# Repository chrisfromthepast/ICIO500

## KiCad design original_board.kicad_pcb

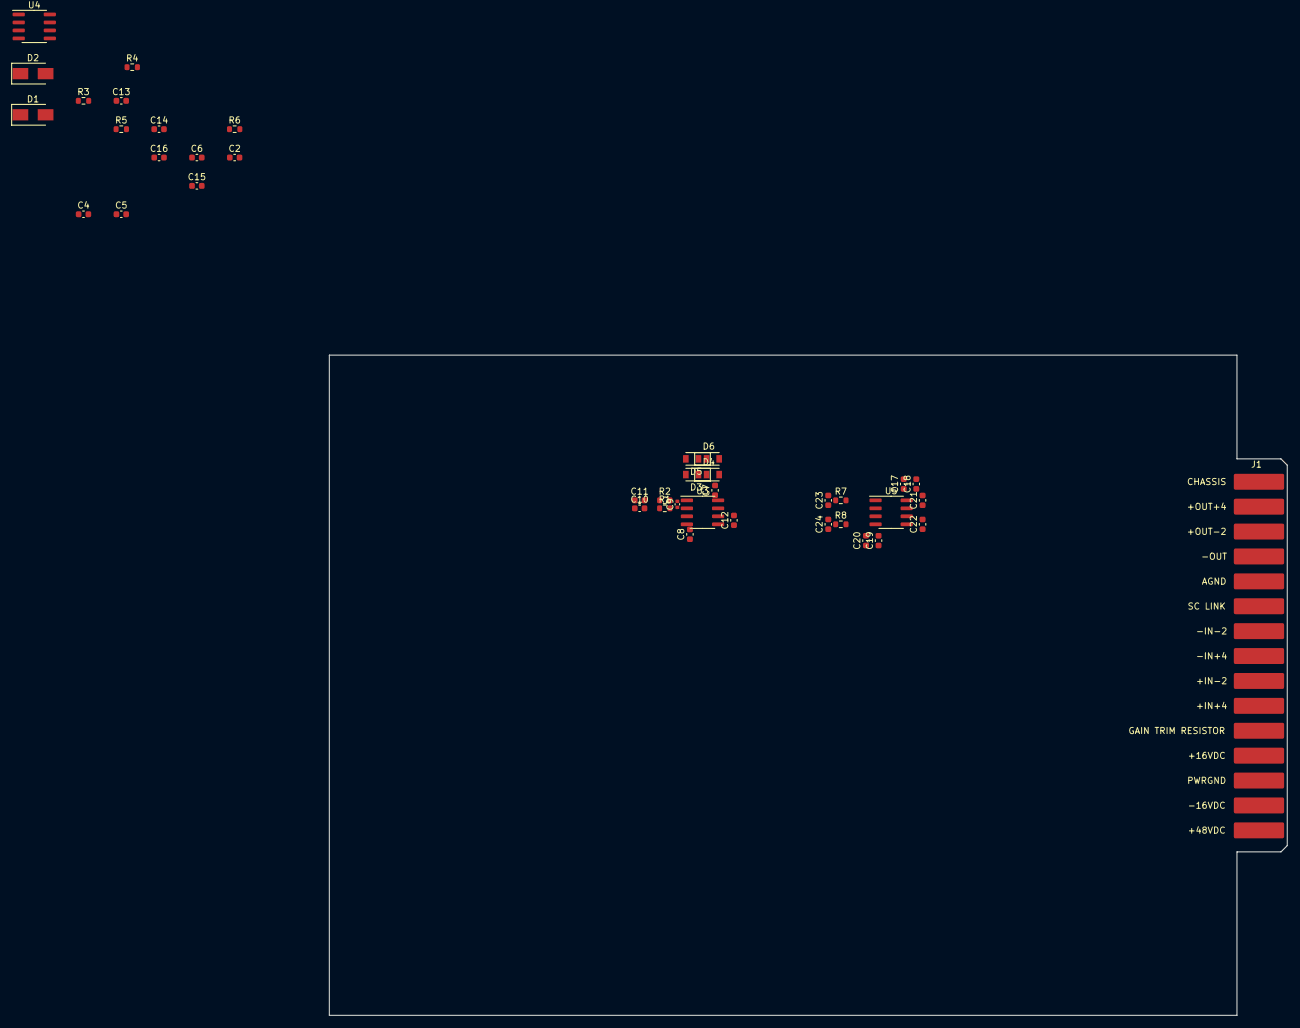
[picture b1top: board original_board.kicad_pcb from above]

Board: 2 copper layers, 152.3 x 105.0 mm, 40 parts (0 on the bottom side), 23 nets, no tracks yet.

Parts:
C2, C4, C5, C6, C7, C8, C10, C11, C12, C13, C14, C15, C16, C17, C18, C19, C20, C21, C22, C23, C24: C0603
C9: C0402
D1, D2: ?; D_SMA
D3, D4, D5, D6: ?; D_SOD-123
J1: EDA 306; EDA_306
R1, R2, R3, R4, R5, R6, R7, R8: R0603
U3, U4, U5: ?; SOIC-8_3.9x4.9mm_P1.27mm

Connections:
audio_out: R3.1, U3.7
audio_out_to_1646: C16.1, R6.1, U4.7, U5.5
cm: C12.1, U3.6
daisy_5v_power: C5.1, C6.1
daisy_audio_in: C15.1, R4.1, U4.1
daisy_digital_gnd: C5.2, C6.2
driver.r_zobel_minus-vcc: C24.1, R8.2
driver.r_zobel_plus-vcc: C23.1, R7.2
gnd: C2.2, C4.2, C7.2, C8.2, C13.2, C14.2, C17.2, C18.2, C19.2, C20.2, C23.2, C24.2, U3.1, U5.4
in_minus: C11.2, U3.2
in_minus_1: C15.2, R3.2, R4.2, U4.2
in_minus_2: C16.2, R5.2, R6.2, U4.6
in_plus: C10.2, U3.3
out_minus: C22.1, R8.1, U5.3
out_plus_4dbu: C21.1, R7.1, U5.1
receiver.r_rf_minus-vcc: C9.2, C11.1, R2.2
receiver.r_rf_plus-vcc: C9.1, C10.1, R1.2
sense_minus: C22.2, U5.7
sense_plus: C21.2, U5.8
sm: C12.2, U3.5
v_bias_2v5: U4.3, U4.5
v_minus: C4.1, C8.1, C14.1, C19.1, C20.1, U3.4, U4.4, U5.2
v_plus: C2.1, C7.1, C13.1, C17.1, C18.1, U3.8, U4.8, U5.6

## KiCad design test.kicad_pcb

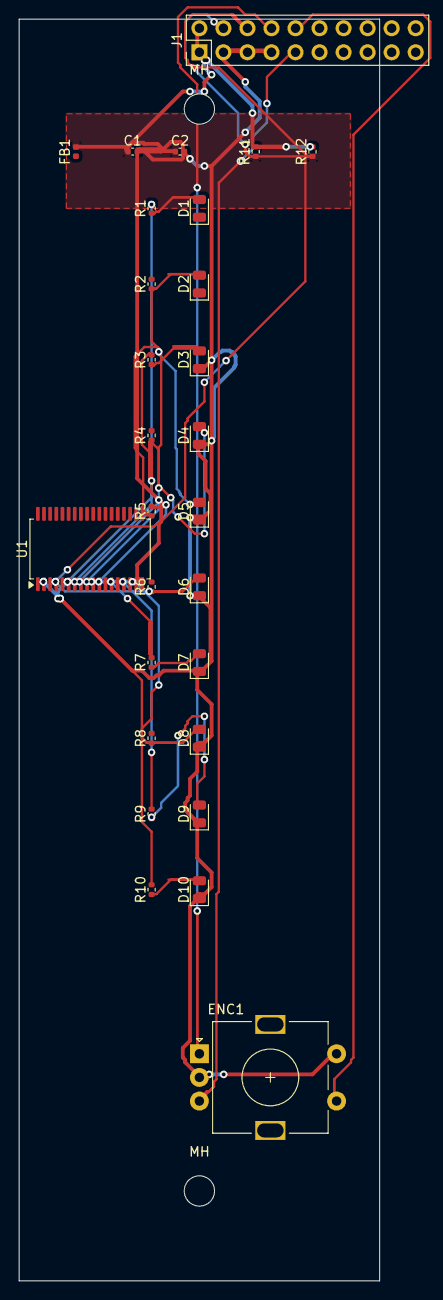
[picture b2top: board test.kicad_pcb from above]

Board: 2 copper layers, 38.1 x 133.3 mm, 30 parts (0 on the bottom side), 27 nets.

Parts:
C1: 10uF; C_0402_1005Metric
C2: 100nF; C_0402_1005Metric
D1, D2, D3, D4, D5, D6, D7, D8, D9, D10: LED; LED_0805_2012Metric
ENC1: EC11E; RotaryEncoder_Alps_EC11E-Switch_Vertical_H20mm
FB1: BLM18PG; L_0402_1005Metric
J1: ?; PinHeader_2x10_P2.54mm_Vertical
MH: MountingHole_3.2mm_M3
MH#2: MountingHole_3.2mm_M3
R1, R2, R3, R4, R5, R6, R7, R8, R9, R10: 33R; R_0402_1005Metric
R11, R12: 4.7k; R_0402_1005Metric
U1: IS31FL3236; TSSOP-36_6.1x12.5mm_P0.65mm

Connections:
+3V3: C1.1, C2.1, FB1.2, J1.1, J1.2, R11.2, R12.2, U1.1, U1.5
ENC_A: ENC1.A, J1.8
ENC_B: ENC1.B, J1.9
ENC_SW: ENC1.S1, J1.10
GND: C1.2, C2.2, D1.1, D2.1, D3.1, D4.1, D5.1, D6.1, D7.1, D8.1, D9.1, D10.1, ENC1.C, ENC1.S2, J1.3, J1.5, J1.7, U1.2, U1.6
LED_1: R1.2, U1.7
LED_1_MID: D1.2, R1.1
LED_2: R2.2, U1.8
LED_2_MID: D2.2, R2.1
LED_3: R3.2, U1.9
LED_3_MID: D3.2, R3.1
LED_4: R4.2, U1.10
LED_4_MID: D4.2, R4.1
LED_5: R5.2, U1.11
LED_5_MID: D5.2, R5.1
LED_6: R6.2, U1.12
LED_6_MID: D6.2, R6.1
LED_7: R7.2, U1.13
LED_7_MID: D7.2, R7.1
LED_8: R8.2, U1.14
LED_8_MID: D8.2, R8.1
LED_9: R9.2, U1.15
LED_9_MID: D9.2, R9.1
LED_10: R10.2, U1.16
LED_10_MID: D10.2, R10.1
SCL: J1.6, R12.1, U1.4
SDA: J1.4, R11.1, U1.3
